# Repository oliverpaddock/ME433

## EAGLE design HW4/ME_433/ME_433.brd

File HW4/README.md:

## Board layout:

## Schematic:

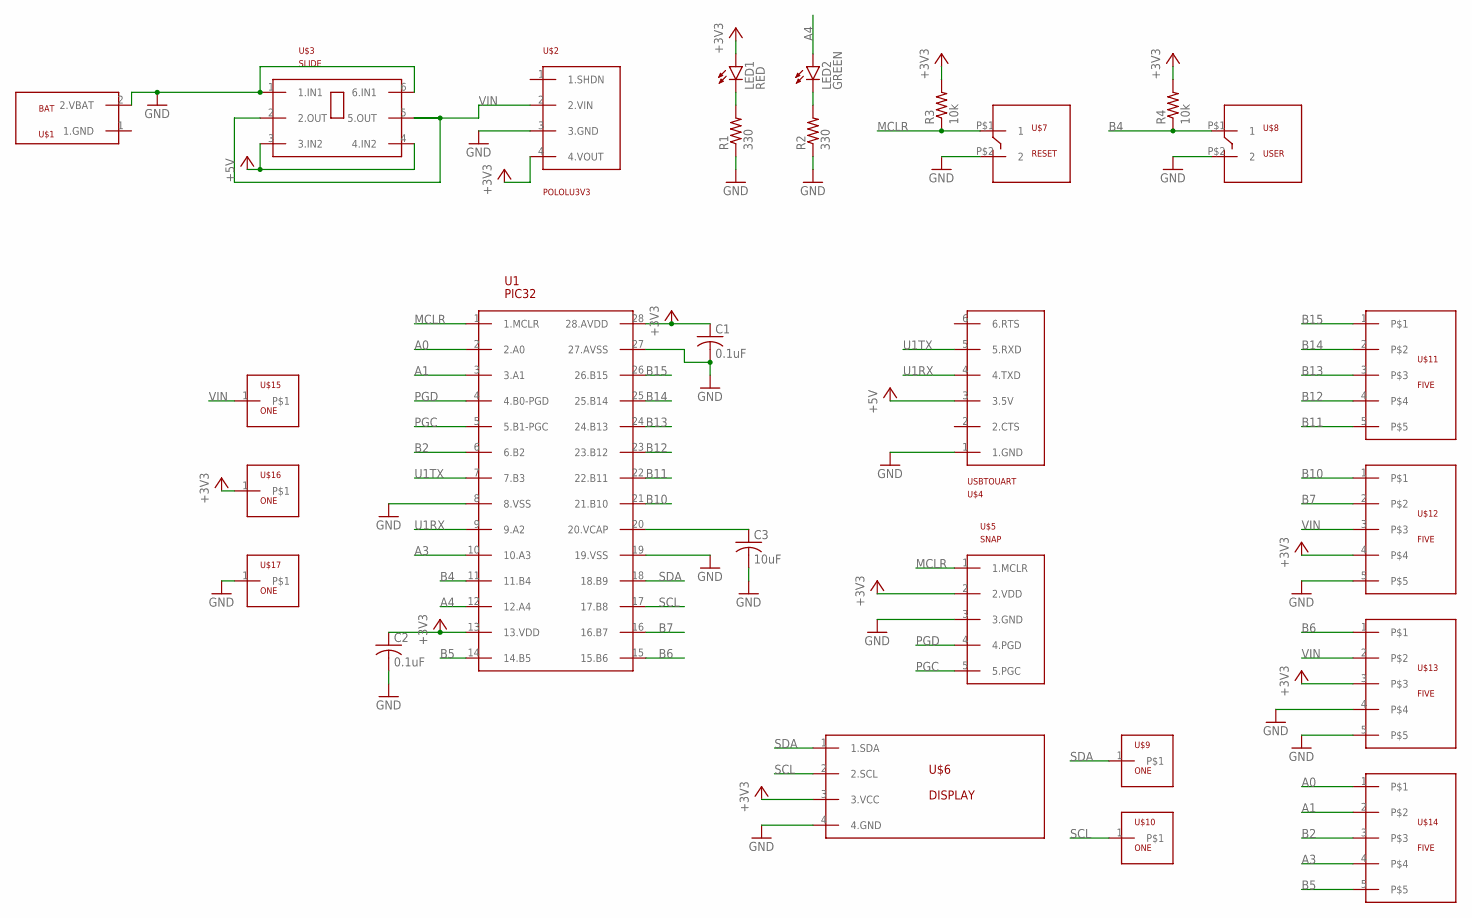
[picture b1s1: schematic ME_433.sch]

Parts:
C1, C2: 0.1uF; C025-024X044
C3: 10uF; C025-024X044
LED1: RED; LED3MM
LED2: GREEN; LED3MM
R1, R2: 330; 0207/7
R3, R4: 10k; 0207/7
U1: PIC32; DIL28-3
U$1: BAT
U$2: POLOLU3V3
U$3: SLIDE
U$4: USBTOUART
U$5: SNAP
U$6: DISPLAY
U$7: RESET; PUSH
U$8: USER; PUSH
U$9, U$10, U$15, U$16, U$17: ONE
U$11, U$12, U$13, U$14: FIVE

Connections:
+3V3: C1.1, C2.1, LED1.A, R3.2, R4.2, U1.13 (13.VDD), U1.28 (28.AVDD), U$2.4 (4.VOUT), U$5.2 (2.VDD), U$6.3 (3.VCC), U$12.4, U$13.3, U$16.1
+5V: U$3.3 (3.IN2), U$3.4 (4.IN2), U$4.3 (3.5V)
A0: U1.2 (2.A0), U$14.1
A1: U1.3 (3.A1), U$14.2
A3: U1.10 (10.A3), U$14.4
A4: LED2.A, U1.12 (12.A4)
B2: U1.6 (6.B2), U$14.3
B4: R4.1, U1.11 (11.B4), U$8.P$1 (1)
B5: U1.14 (14.B5), U$14.5
B6: U1.15 (15.B6), U$13.1
B7: U1.16 (16.B7), U$12.2
B10: U1.21 (21.B10), U$12.1
B11: U1.22 (22.B11), U$11.5
B12: U1.23 (23.B12), U$11.4
B13: U1.24 (24.B13), U$11.3
B14: U1.25 (25.B14), U$11.2
B15: U1.26 (26.B15), U$11.1
GND: C1.2, C2.2, C3.2, R1.1, R2.1, U1.8 (8.VSS), U1.19 (19.VSS), U1.27 (27.AVSS), U$1.2 (2.VBAT), U$2.3 (3.GND), U$3.1 (1.IN1), U$3.6 (6.IN1), U$4.1 (1.GND), U$5.3 (3.GND), U$6.4 (4.GND), U$7.P$2 (2), U$8.P$2 (2), U$12.5, U$13.4, U$13.5, U$17.1
MCLR: R3.1, U1.1 (1.MCLR), U$5.1 (1.MCLR), U$7.P$1 (1)
unnamed: LED1.K (C), R1.2
unnamed: LED2.K (C), R2.2
unnamed: C3.1, U1.20 (20.VCAP)
PGC: U1.5 (5.B1-PGC), U$5.5 (5.PGC)
PGD: U1.4 (4.B0-PGD), U$5.4 (4.PGD)
SCL: U1.17 (17.B8), U$6.2 (2.SCL), U$10.1
SDA: U1.18 (18.B9), U$6.1 (1.SDA), U$9.1
U1RX: U1.9 (9.A2), U$4.4 (4.TXD)
U1TX: U1.7 (7.B3), U$4.5 (5.RXD)
VIN: U$2.2 (2.VIN), U$3.2 (2.OUT), U$3.5 (5.OUT), U$12.3, U$13.2, U$15.1

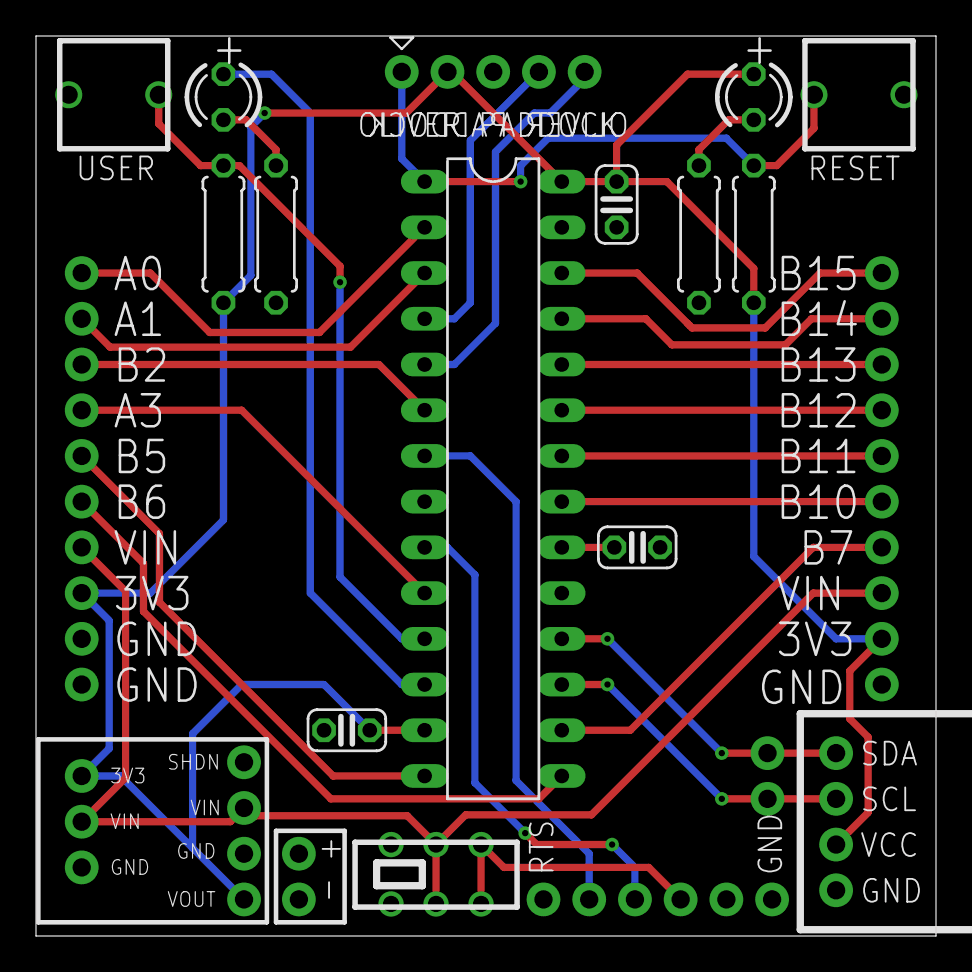
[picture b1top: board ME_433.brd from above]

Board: 2 copper layers, 50.0 x 50.0 mm, 27 parts (0 on the bottom side), 29 nets.

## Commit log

2022-04-05 added circuit diagram
2022-04-05 added circuit picture
2022-04-05 renamed files
2022-04-17 added HW4
2022-05-24 HW10
2022-06-10 HW11
2022-06-10 HW12
